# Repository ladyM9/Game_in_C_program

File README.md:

# Game_in_C_program
This project is based on the STM32H742ZIT6, with games displayed on the TFT LCD display.
The menu is navigated using a joystick, and the games are played using an accelerometer.

 In this repository, you can find a scaling script (written in Python) for scaling a maze for display on an LCD TFT, as well as the main code used to display the menu and games. Other parts of the code describe the menu, the first game, the second game, and the objects in the games.

## ***Contents of repo***
-   Main code
-   Maze scaling script
-   Schema and PCB

## ***Features***
-   Two games
-   Power with using battery
-   Controlling with objects in games using the acelerometer
-   The history of game scores

## ***Game console overview***

<p align="center">
    
    <br>
        <b>Main Menu Overview</b>
</p>
<br>

<p align="center">
    
    <br>
        <b>Maze game</b>
</p>
<br>

<p align="center">
    
    <br>
        <b>Pong game</b>
</p>
<br>

<p align="center">
    
    <br>
        <b>Highscore screen</b>
</p>
<br>

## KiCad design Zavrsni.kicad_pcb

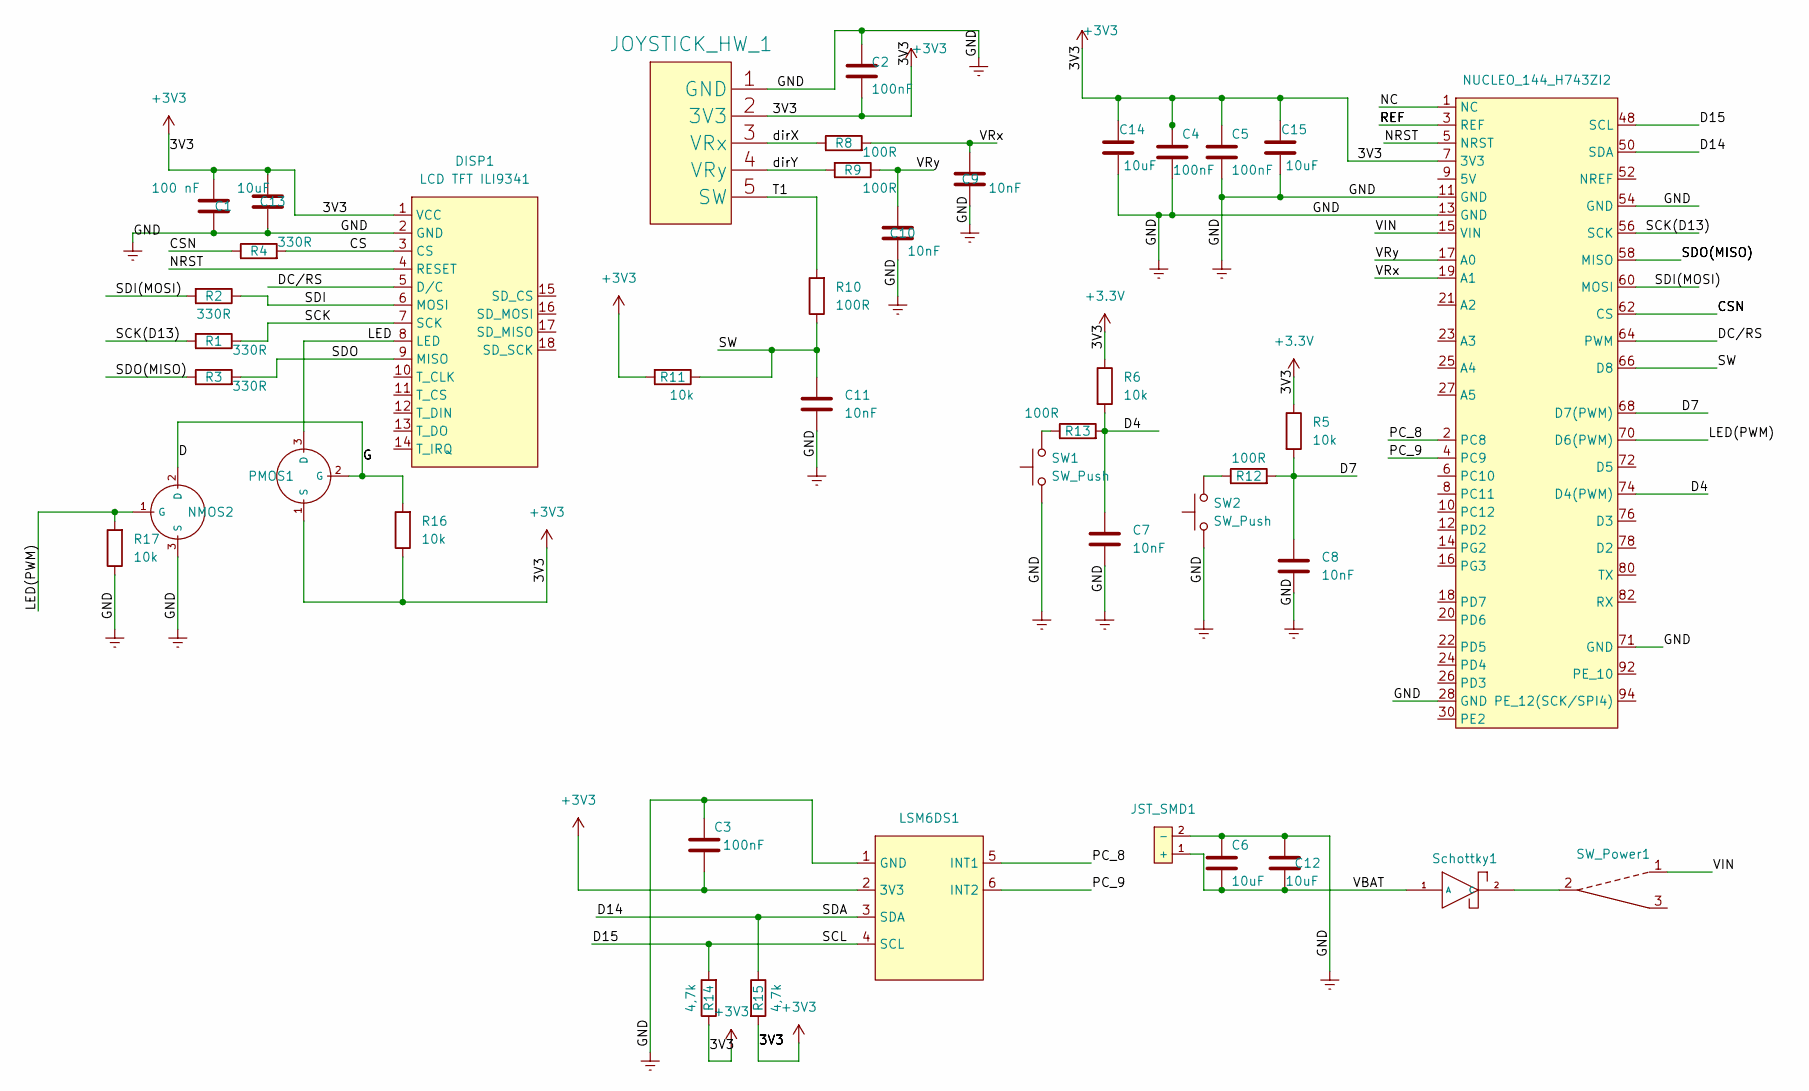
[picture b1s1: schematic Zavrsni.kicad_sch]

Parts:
C1: 100 nF; C_0603_1608Metric
C2, C3, C4, C5: 100nF; C_0603_1608Metric
C6, C12, C13, C14, C15: 10uF; C_1206_3216Metric
C7, C8, C9, C10, C11: 10nF; C_0603_1608Metric
DISP1: LCD TFT ILI9341; LCD_TFT_2.4
JOYSTICK_HW_1: JOYSTICK
JST_SMD1: JST_SMD
LSM6DS1: LSM6DS3
NMOS2: SOT-23-3
NUCLEO_144_H743ZI2: NUCLEO_PCB
PMOS1: SOT-23-3
R1, R2, R3, R4: 330R; R_0603_1608Metric
R5, R6: 10k; C_0603_1608Metric
R8, R9, R10, R12, R13: 100R; R_0603_1608Metric
R11, R16, R17: 10k; R_0603_1608Metric
R14, R15: 4,7k; R_0603_1608Metric
SW1, SW2: SW_Push; SW_SPST_SKQG_WithoutStem
SW_Power1: Power_Switch
Schottky1: Schottky_D

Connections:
+3.3V: C1.1, C2.2, C3.2, C4.1, C5.1, C13.2, C14.1, C15.1, DISP1.1 (VCC), JOYSTICK_HW_1.2 (3V3), LSM6DS1.2 (3V3), NUCLEO_144_H743ZI2.7 (3V3), PMOS1.1 (S), R5.1, R6.1, R11.2, R14.1, R15.2, R16.1
/CS: DISP1.3 (CS), R4.2
/CSN: NUCLEO_144_H743ZI2.62 (CS), R4.1
/D: NMOS2.2 (D), PMOS1.2 (G), R16.2
/D4: C7.1, NUCLEO_144_H743ZI2.74 (D4(PWM)), R6.2, R13.2
/D7: C8.1, NUCLEO_144_H743ZI2.68 (D7(PWM)), R5.2, R12.2
/D14: LSM6DS1.3 (SDA), NUCLEO_144_H743ZI2.50 (SDA), R15.1
/D15: LSM6DS1.4 (SCL), NUCLEO_144_H743ZI2.48 (SCL), R14.2
/DC/RS: DISP1.5 (D/C), NUCLEO_144_H743ZI2.64 (PWM)
/LED: DISP1.8 (LED), PMOS1.3 (D)
/LED(PWM): NMOS2.1 (G), NUCLEO_144_H743ZI2.70 (D6(PWM)), R17.2
/NC: NUCLEO_144_H743ZI2.1 (NC)
/NRST: DISP1.4 (RESET), NUCLEO_144_H743ZI2.5 (NRST)
/PC_8: LSM6DS1.5 (INT1), NUCLEO_144_H743ZI2.2 (PC8)
/PC_9: LSM6DS1.6 (INT2), NUCLEO_144_H743ZI2.4 (PC9)
/REF: NUCLEO_144_H743ZI2.3 (REF)
/SCK: DISP1.7 (SCK), R1.1
/SCK(D13): NUCLEO_144_H743ZI2.56 (SCK), R1.2
/SDI: DISP1.6 (MOSI), R2.1
/SDI(MOSI): NUCLEO_144_H743ZI2.60 (MOSI), R2.2
/SDO: DISP1.9 (MISO), R3.2
/SDO(MISO): NUCLEO_144_H743ZI2.58 (MISO), R3.1
/SW: C11.1, NUCLEO_144_H743ZI2.66 (D8), R10.1, R11.1
/T1: JOYSTICK_HW_1.5 (SW), R10.2
/VBAT: C6.2, C12.2, JST_SMD1.1 (+), Schottky1.1 (A); also elsewhere on the board
/VIN: NUCLEO_144_H743ZI2.15 (VIN), SW_Power1.1
/VRx: C9.1, NUCLEO_144_H743ZI2.19 (A1), R8.2
/VRy: C10.1, NUCLEO_144_H743ZI2.17 (A0), R9.1
/dirX: JOYSTICK_HW_1.3 (VRx), R8.1
/dirY: JOYSTICK_HW_1.4 (VRy), R9.2
Earth: C1.2, C2.1, C3.1, C4.2, C5.2, C6.1, C7.2, C8.2, C9.2, C10.2, C11.2, C12.1, C13.1, C14.2, C15.2, DISP1.2 (GND), JOYSTICK_HW_1.1 (GND), JST_SMD1.2 (-), LSM6DS1.1 (GND), NMOS2.3 (S), NUCLEO_144_H743ZI2.11 (GND), NUCLEO_144_H743ZI2.13 (GND), NUCLEO_144_H743ZI2.28 (GND), NUCLEO_144_H743ZI2.54 (GND), NUCLEO_144_H743ZI2.71 (GND), R17.1, SW1.1, SW2.1
unnamed: R12.1, SW2.2
unnamed: R13.1, SW1.2
unnamed 33: SW_Power1.2, Schottky1.2 (C); also elsewhere on the board

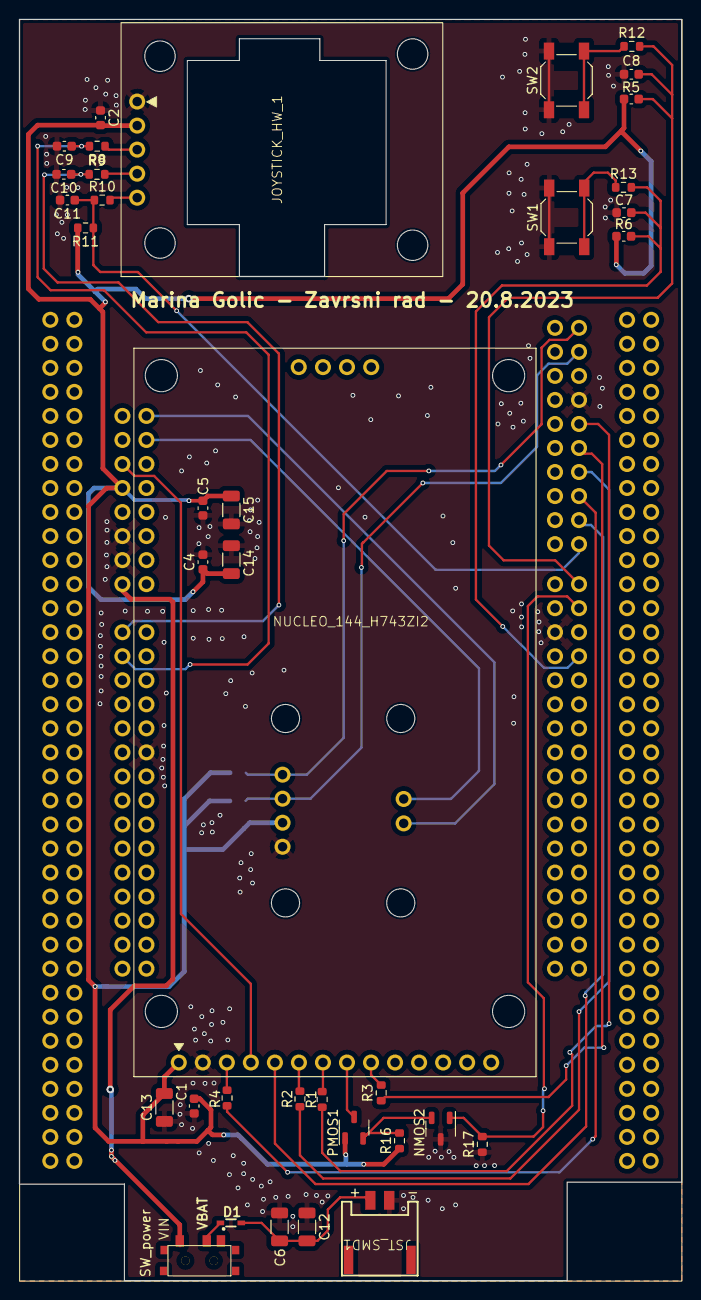
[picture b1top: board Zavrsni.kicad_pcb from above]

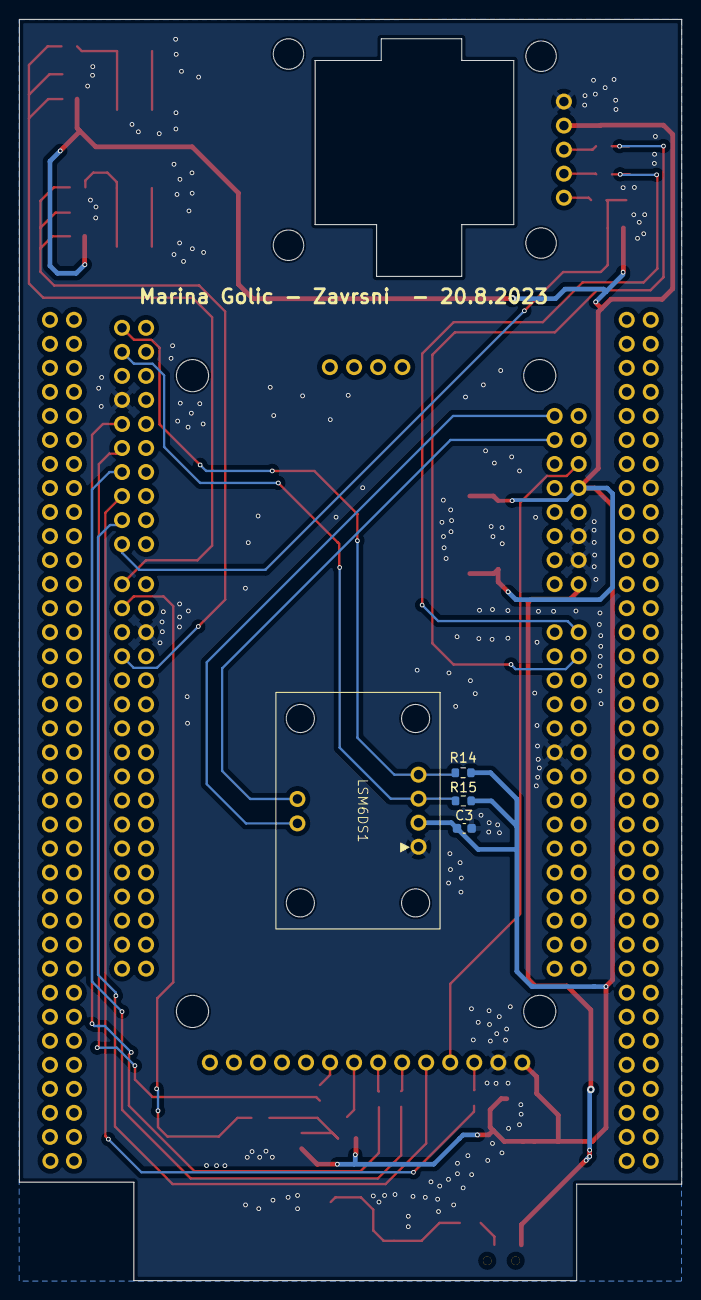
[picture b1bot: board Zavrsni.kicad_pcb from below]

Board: 2 copper layers, 70.0 x 133.3 mm, 42 parts (4 on the bottom side), 32 nets.

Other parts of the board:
D1: Schottky_D

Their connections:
/VBAT: D1.1 (A); also elsewhere on the board
unnamed 33: D1.2 (C); also elsewhere on the board

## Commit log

2021-03-17 Add files via upload
    Pokušaj kolizije pomoću funkcije
2021-03-18 Uspjesna kolizija, dodavanje strukture
2021-05-02 Add files via upload
    Kolizija se dogodi na lijevo,desno i dolje
2021-05-03 Add files via upload
    Kolizija za top i bottom radi samo na liniji kad krug dotakne dakle ne van te linije
2021-05-06 Add files via upload
    Pokušaj prvog labirinta, kolizija radi samo na jednoj crti
2021-05-15 Add files via upload
    Pokusaj algoritma lab pomocu polja struktura
2021-05-17 Add files via upload
    Prvi labirint koji je iscrtan preko cijelog display-a, sve linije se nalaze unutar jednog polja strukture, kuglica dodana na display
2021-05-18 Add files via upload
    Napravljen izlaza iz labirinta i pokušaj da kad točkica dođe na izlaz da piše "YOU WON"
2021-05-19 Add files via upload
    Dodan i iscrtan još drugi labirint
2021-05-20 Add files via upload
    Kad kuglica dođe na izlaz iz labirinta ispiše se YOU WON
2021-05-21 Add files via upload
    Pokusšaj izbornika
2021-05-24 Add files via upload
    Pokušaj izbornika za odabir igrice i sređivanje koda
2021-05-28 Add files via upload
    Ne rade kolizije
2021-05-28 Add files via upload
    Radi kolizija na izlazu iz labirinta, podjeljen kod u 2 dadoteke
2021-05-31 Add files via upload
    Pokušaj detekcije kolizije na svaku liniju, kuglica se nalazi na početnoj poziciji
2022-02-23 Added custom STM32H743 clock config for faster SPI
2022-02-26 Add files via upload
    Pokušaj kolizije
2022-03-03 Add files via upload
    Ispravna detekcija kad se dotakne linija ali ne radi baš najbolje jer detektira i u prostoru gdje nema linije
2022-03-03 Add files via upload
    Detektira da je kuglica dotaknila liniju ali i detektira "fail" i u praznom prostoru???
2022-03-10 Fixed collisions (works!), removed some unused code
    Removed some of unused and commented code, removed Serial.begin() inside of loop(), fixed collision detection (it's finally working!).
2022-03-15 Add files via upload
    Pokušaj da kad kuglica dođe na izlaz iz labirinta da se prepozna kolizija i da se ispiše you win
2022-03-16 Add files via upload
    Kolizija radi, ispisuje se linija za izlaz ali kolizija za izlaz ne radi dobro
2022-03-18 Kolizija na izlazu iz labirinta radi
2022-03-22 Dodan još jedan labirint
    Kolizija ne radi najbolje, i labirint se ne iscrtava do kraja display-a
2022-03-24 beginning creation in maze game
2022-03-30 The maze is scaled and collisions work, but output of maze does not work
2022-04-02 New scale of maze, but it is not correct
2022-04-04 Added C code for extracting lab lines
    Converts lines from .svg file from www.mazegenerator.net into Arduino .h file with x1, y1, x2 and y2 coordinates.
2022-04-06 Bouncing circle on x direction, and have a new maze
2022-04-08 Bouncing ball on x and y direction
2022-04-08 Fixed lab extract script
    Filename of .svg file can have spaces now.
    Added "Press any key to exit" at the end of the code.
    Added fclose() after data parsing.
2022-04-25 Bug with ball is resolved, ball is on correct possition on beggining of game
2022-04-29 Added time in game
2022-05-04 Time in game is correct now, but in game have a new bug with collisions
2022-05-06 New bug with time in game, and optimize programm with fuctions
2022-05-13 Problem with print game over on display
2023-01-17 Labirint se u igricu stavlja pomoću .h filea
2023-01-21 Removed ALL old and unused files
2023-01-21 Compile error fixed, added comments, code clean-up
2023-01-21 Create .clang-format
2023-01-21 Files moved to the sketch folder
2023-01-21 Typo on gitignore
2023-01-22 Fixed maze list / array name.
2023-01-23 Made collisions on lines and at checkpoints
2023-01-25 Skript for scalling and resizing maze
2023-01-30 One line in maze is resized
2023-02-04 Successfully scaled maze
    Successfully scaled maze, but the script does not write to the correct scaled maze file
2023-02-08 The problem with lines in maze has been solved
2023-02-14 Added two more mazes
2023-03-10 Fail...Nothing is print on display
2023-03-13 The ball is drawn on the screen using the class
2023-03-17 Ball is moving on display
2023-03-22 Maze is not draw to display
2023-03-30 Problem with callback function
2023-04-04 Nothing is print to display with function callback
2023-04-04 Finally display is refreshing and the ball is moving using a class.
2023-04-14 Attempt colision detection
2023-04-20 Maze is print on display, but collision is not working
2023-04-21 Collision decetion on x direction
2023-04-24 Collision detection on x direction and y direction but on y direction ball is not bouncing
2023-04-27 Collision detection is not work
2023-05-03 Collision detection is not working on x os
2023-05-10 Code update and added very important comments in the code.
2023-05-10 code is not ok, in code is many error
    First error is empty fields, second incorrect deletion and flag setting, third you don't need the draw Circle function
2023-05-11 adding comments
2023-05-11 Comments for code fix.
2023-05-12 Added h file with maze, many error is corected
2023-05-16 New code with correct detection collision
2023-05-17 Added exit line and prepared text for printing time
2023-05-23 After time is over, the second maze is draw on display
2023-05-26 Added random number function and one more maze, but problem with time in game
2023-06-03 Adding intervals of time in game, but game is not work correctly, (ball is not moving)
2023-06-06 Printing random maze on display after the collision between ball and exit line
2023-06-13 Add switch case
2023-06-17 Finally fixed mazes switching after completing a maze, code clean-up, file clean-up.
2023-06-18 Added comments in code
2023-06-27 Finally a correct drawing of the maze with proper scaling
2023-06-27 Corretct parsing svg file
2023-07-02 Finaly all parsing mazes writening in h file
2023-07-04 Problem with exit line
2023-07-06 Made exit line of maze and scaling start position and exit line, and added comments
2023-07-10 Starting create GUI in game
2023-07-20 Moving y cordinate 20 pixels beacuse writing score and time game on display, add score game and add comments
2023-07-22 [ladyM9] printing score screen, after the exit of maze
2023-07-22 Added sketch folder.
2023-07-25 Added acceleration to the game
2023-07-29 Aceleometer is not working with SparkFunLSM6DS3 library
2023-07-30 the cursor in the main menu does not go outside the display and acceleration in the game works
2023-07-31 fixed bug with game mode selection, extended output line, and added image representing the point that can be won in the game
2023-08-02 The exit line is properly scaled, by calculating the distance between the 2 lines
2023-08-04 Create Schema and PCB for game
2023-08-04 Schema and pcb for game
2023-08-06 Added push buttons, and footprint for JST connector
2023-08-07 Start connecting the lines on the pcb
2023-08-11 [ladyM9] LSM is placed on the bottom side of the PCB, vias are reduced, buttons are placed and connected to the PCB
2023-08-12 All components on the PCB are connected
2023-08-13 Add power switch, poligon for GND, and flip lsm on bottom
2023-08-13 switch error, the wrong switch was selected and connected incorrectly in the schematic
2023-08-14 Shifted pins on the nucleo board, up the y axis
2023-08-16 The pcb is assembled, but the pin spacing is incorrect
2023-08-17 The pcb is cut for the buttons on the NUCLEO board
2023-08-17 Added one more game in project, the game is pong game
2023-08-19 Finnal version of PCB and schema
2023-08-19 Add collision detection in Pong game
2023-08-20 Finall version of PCB without gerbers
2023-09-14 Display has been rotated because displayed game
2023-09-14 paddle.h and paddle.cpp has been deleted, commit by ladyM9
2023-09-15 After the push the back button, the menu has been open a
    And after 60 seconds in game, display the game over screen
2023-09-17 After 60 seconds in game, the user lose 1 life if he don t on exit line
2023-09-22 after the game time runs out, the player loses a life
2023-09-22 If result of score in game is null, user lost the live
2023-10-01 Added loading screen with pictures
2023-10-03 Fixed bug in pong game
2023-10-18 Files divided into folders
2023-11-30 Added picture
2024-02-19 Resolved problem with merge
2024-10-02 Added pictures in repo
2024-10-02 Deleted the some files
2024-10-02 Added two pictures
2024-10-04 Bettter organization of files
